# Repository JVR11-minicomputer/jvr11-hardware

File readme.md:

# JVR11 Homebrew Minicomputer - Hardware

This repository contains all schematics, PCB designs and PLD design sources of the JVR11, a homebrew minicomputer built around the DEC DCJ11 microprocessor. The computer will be built in multiple phases, each described in detail below.

All schematics and PCBs are designed in KiCad. All designs targeting SPLDs like the GAL16V8 and 22V10 are designed in WinCUPL, except the old sources, which were designed in GALASM. These will be replaced later. The CPLDs I used are all part of the ATF1504AS series, which can be used as an alternative to the MAX7000 series. All RTL is written in SystemVerilog and compiled using an older version of Quartus, targeting the MAX7000 series. The outputs were then converted to JEDEC using Atmel's POF2JED tool.

## Goals
### Phase 1: ODT Console    (FINISHED)

This is the very first stage of the project. My goal is to build a minimal but functional system capable of running a simple program. All the computer needs is a UART used to interact with the built-in ODT console and a little bit of SRAM to peek/poke into. This UART interface is built around the (Harris) 6402. Programs can be entered manually into memory and executed using this console, so no ROM is required. The ODT console itself is implemented in the processor's microcode.

The computer also needs to be able to load some startup configuration from a special register during its power-up sequence. A GAL22V10 is used as an interface to this register, I call it the "GP-interface". "GP" refers to the general-purpose cycles, which is a special kind of bus transaction that plays a big role during the power-up sequence. In addition, this interface is also responsible for generating the bus-reset signal and driving some status LEDs indicating whether the processor is in its "ODT mode" and also the results of the three microdiagnostics tests. All of this will be moved to the front panel later.

Known problems:
- The reset pin of the UART seems to be very sensitive to noise. When it is driven by the bus-reset signal, it starts to misbehave. This is because everything is still built on breadboards, which is definitely not ideal for this kind of builds. As a temporary solution, I connected a schmitt trigger inverter (74HCT14) to the active-low bus-reset to form a more stable reset signal for the UART. This inverter is probably not required anymore once the circuit moves to PCB, especially since the bus-reset signals will get buffered anyways.

### Phase 2: Bus Controller Upgrade     (IN PROGRESS)
In the previous phase, the computer used a single GAL16V8 to generate the bus access strobes (read enable, write enable etc). While being sufficient for a minimal functional system, it lacks a lot of functionality that we'll depend on later. This phase is all about implementing this missing functionality. First of all, it lacks the possibility to extend the cycle by inserting wait states. This will be required when interacting with slower IO devices and also in case of a cache miss. Second, since I'm planning to add DMA in the future, we need to support bus arbitration in order to be able to request mastership over the bus. Finally, we did not care about abort conditions. The internal MMU is capable of generating internal error conditions in which the remainder of the current cycle must be ignored and the access strobes are to be inhibited. An abort can also be generated by external hardware, but under specific conditions. In our case the system may report an error when referring to non-existent memory/IO or when writing to a read-only location or reading from a write-only location.

### Phase 3: Memory Subsystem     (FINISHED)
~~Every computer needs random-access memory. The J11 is capable of addressing 4MiB of physical memory of which the top 8K is reserved for memory-mapped IO. The remainder will be filled by RAM and a bit of ROM. Filling almost 4MiB with SRAM is practically possible with modern chips, but that would violate one of my most important constraints: keeping it as historically correct as possible. Therefore I will be using asynchronous DRAM.~~ 

~~Dynamic memory has two serious disadvantages: it's slow and needs periodic refreshes, or the data you stored will be lost. When it comes to refreshing the memory at regular intervals, I want to keep it as transparent to the CPU as possible by implementing a dedicated controller that runs on its own clock domain. When it comes down to the DRAM speeds, a single layer of write-back direct-mapped cache will be added which will act as a faster buffer between the fast system and its slow memory. The cache will offer 32KiB of SRAM to buffer both instructions and data (still unified), organized as 8K 32-bit cache blocks.~~

My original goal was to use DRAM for the system's main memory, using a dedicated controller that makes the access timing and refreshing completely transparent to the rest of the system. Since DRAM is slow, I wanted to introduce a write-back cache. I ended up moving the cache into the memory subsystem rather than keeping it local to the processor, which might sound like a questionable design choice (I admit it is), but it solved all coherency related problems because all memory accesses go through the same cache, even those initiated by the DMA controller.

I spent a couple of months working out a datapath and a control path and ended up with something that seamed to work, but it had some problems. The DRAM controller became a bottleneck, its worst-case latency was so high it was just unacceptable. I must mention one of my constraints for this project: I do not want to use any programmable logic device more capable than a simple MAX7000 CPLD with 64 macrocells. The overall performance can be greatly improved by designing a better DRAM controller, but that would require a lot more than 64 macrocells.

Improving the current memory system is simply impossible given my constraints, so I had to make a difficult decision: I decided to roll back to SRAM, which is simple to interface, fast enough to not need caching, but more importantly, it doesn't require a sophisticated memory subsystem anymore.

### Phase 4: IO Bridge  (IN PROGRESS)
Depending on the exact version, the J11 can run at a maximum clock speed of either 15MHz or 18MHz. That is way too fast to interface with slower IO controller chips directly. The simplest solution would be to rely on the wait state mechanism implemented by the bus controller to relax the speeds, but for write cycles that will cause stalls that could be avoided. Instead, a bridge can be added which buffers the write transactions targeting the slower IO devices behind it. The CPU can "deposit" the write data into this bridge at its full operating speed and resume execution while the IO bridge "proxies" that transaction on the slower bus. Unfortunately, read transfers cannot be buffered.

### Phase 5: Interrupts & DMA  (NOT STARTED)
The J11 supports vectored interrupts on multiple priority levels. A dedicated interrupt controller will be required to provide the vector address to the processor during an interrupt acknowledge cycle. I want those vector addresses to be fully programmable.

For high-throughput IO devices DMA can be used to transfer data without the processor's involvement. I want to build a flexible DMA controller that is fully programmable, has multiple channels with internal prioritization, can handle both 8 or 16 bit word sizes, can handle memory-to-memory transfers and can handle chained/scatter-gather transfers. The latter is required since the J11's internal MMU can map non-consecutive pages. Its design is inspired by the Motorola 68450 DMAC.

### Phase 6: Adding More IO  (NOT STARTED)
The most fundamental objective of this project is to build a minicomputer. While there is no real definition of what makes a computer a minicomputer, my interpretation of a minicomputer is a "big" computer that has multi-user capabilities and a lot of IO. From a hardware point of view, this is the moment where the homebrew computer turns into a proper minicomputer. With the IO bridge in place and interrupts and DMA being supported, it is finally time to start adding more and more IO devices to the system. I will add as much as I can, including: storage, timers, displays, sound, and more.

### Phase 7: VGA Subsystem  (NOT STARTED)
I always wanted to build my own VGA subsystem, so this is my chance. I got inspired by two unrelated video controllers: [James Sharman's VGA](https://youtube.com/playlist?list=PLFhc0MFC8MiD2QzxJKi_bHqwpGBZZpYCt&feature=shared) and the IBM PGA. James Sharman built a VGA controller completely from scratch, featuring advanced functionality such as scrolling, beam racing, tilemaps and more. The PGA on the other hand is a less-known video controller made by IBM that had a 8088 on board serving as a coprocessor. It could emulate a CGA, but more interestingly, it could be used to offload high-level commands. These two video controllers are completely different: on one hand we have complex functionality implemented in hardware and on the other we have software emulation. That raises one important question: Can we combine the best of both worlds? Can we build a VGA controller that implements complex functionality in hardware but also features a dedicated coprocessor that can offload things from the J11?

I don't have any concrete plans yet and I don't know how far I will take this, if I can even get to this point. But, I am sure about one thing: the 8088 is a great processor but if I were going to use a coprocessor I'd choose a less common processor. If possible, I want to keep it minicomputer-related. Or even better, DEC-related so both processors share some common history. That left me with one specific processor: the DEC DCT11. The J11 and the T11 both implement the PDP-11 instruction set, but other than that they do not have anything in common.

## Current Status (May 2026)
<br />

In the past two months I have been working on the IO bridge (right) and a new version of the core (left). At this moment, the prototype of the IO bridge is ready to be tested. I want to make sure the new version of the core is completely functional before integrating the IO bridge, hence the reason why the bridge isn't wired up to the computer just yet. 

The most important changes in the newest version computer's core are:
  -  **More memory**: The two 16KiB SRAM chips have been replaced by two 128KiB SRAM chips and ROM has been added.
  -  Bus buffers: In the previous version I used a set of 74x245 bidirectional buffers to drive the databus. Those are replaced by 74x541 unidirectional buffers, mainly for speed and to avoid brief contention when the direction changes while the outputs were active.
  -  **Address decoder**: The temporary decoder has been replaced by what I call the primary decoder. It is still an address decoder, but the main difference is that it selects larger subsystems (minimum 8KiB chunks) rather than individual peripherals like the UART. The new decoder can also generate aborts in case of non-existent memory or access violations (eg. writing to ROM). Until the IO bridge is in place, some temporary logic is used to decode the IO bridge select further down into a chip select for the ODT UART.
  - **Bus Error subsystem**: This is a small subsystem that can help the software to recover from bus errors. It latches additional context like the error type (4 bits) into a register that is readable by the processor and also serves as a configuration register that can enable or disable certain types of bus error. This register will be called the BER (Bus Error Recovery Register), which maps to a currently unused system register. This subsystem will not be used when the CPU is not the bus master since devices like the DMA will use its own error handling semantics.
  - **Bus controller**: The bus controller got a big upgrade. Its intent did not change, but it got a bit more sophisticated. In the last version the controller consisted of a MAX7000 CPLD and a 22V10 because this CPLD did not have enough pins to fit everything on a single chip. Now it has been replaced by a PLCC-84 version this CPLD, which offers more than enough usable pins.

**Next Steps:**

The new core has been built on breadboard and is almost ready to be tested. I am still writing the RTL for the new bus controller. Once the core is finished, the IO bridge can finally be integrated. After that, the next step would be the interrupt controller and finally moving existing parts of the build to PCB.

## Special thanks to PCBWay!
<br />

I would like to sincerely thank PCBWay for sponsoring this project. Their support has been invaluable in bringing this work to life. PCBWay is a leading manufacturer specializing in high-quality printed circuit boards, offering services ranging from rapid PCB prototyping to full-scale production. In addition to PCBs they also provide services like PCB assembly, CNC, 3D printing and more. 

I have been very pleased with the quality of the PCBs and SMD stencils I received. The precision, finish, and reliability exceeded my expectations. Overall, my experience with PCBWay has been excellent. Therefore I highly recommend others to check out [PCBWay](https://www.pcbway.com/) for their own projects.

<br />A picture of the boards I received: <br /><br />

## License
The content of this project is licensed under the [CERN-OHL-P version 2 license](https://cern-ohl.web.cern.ch/).

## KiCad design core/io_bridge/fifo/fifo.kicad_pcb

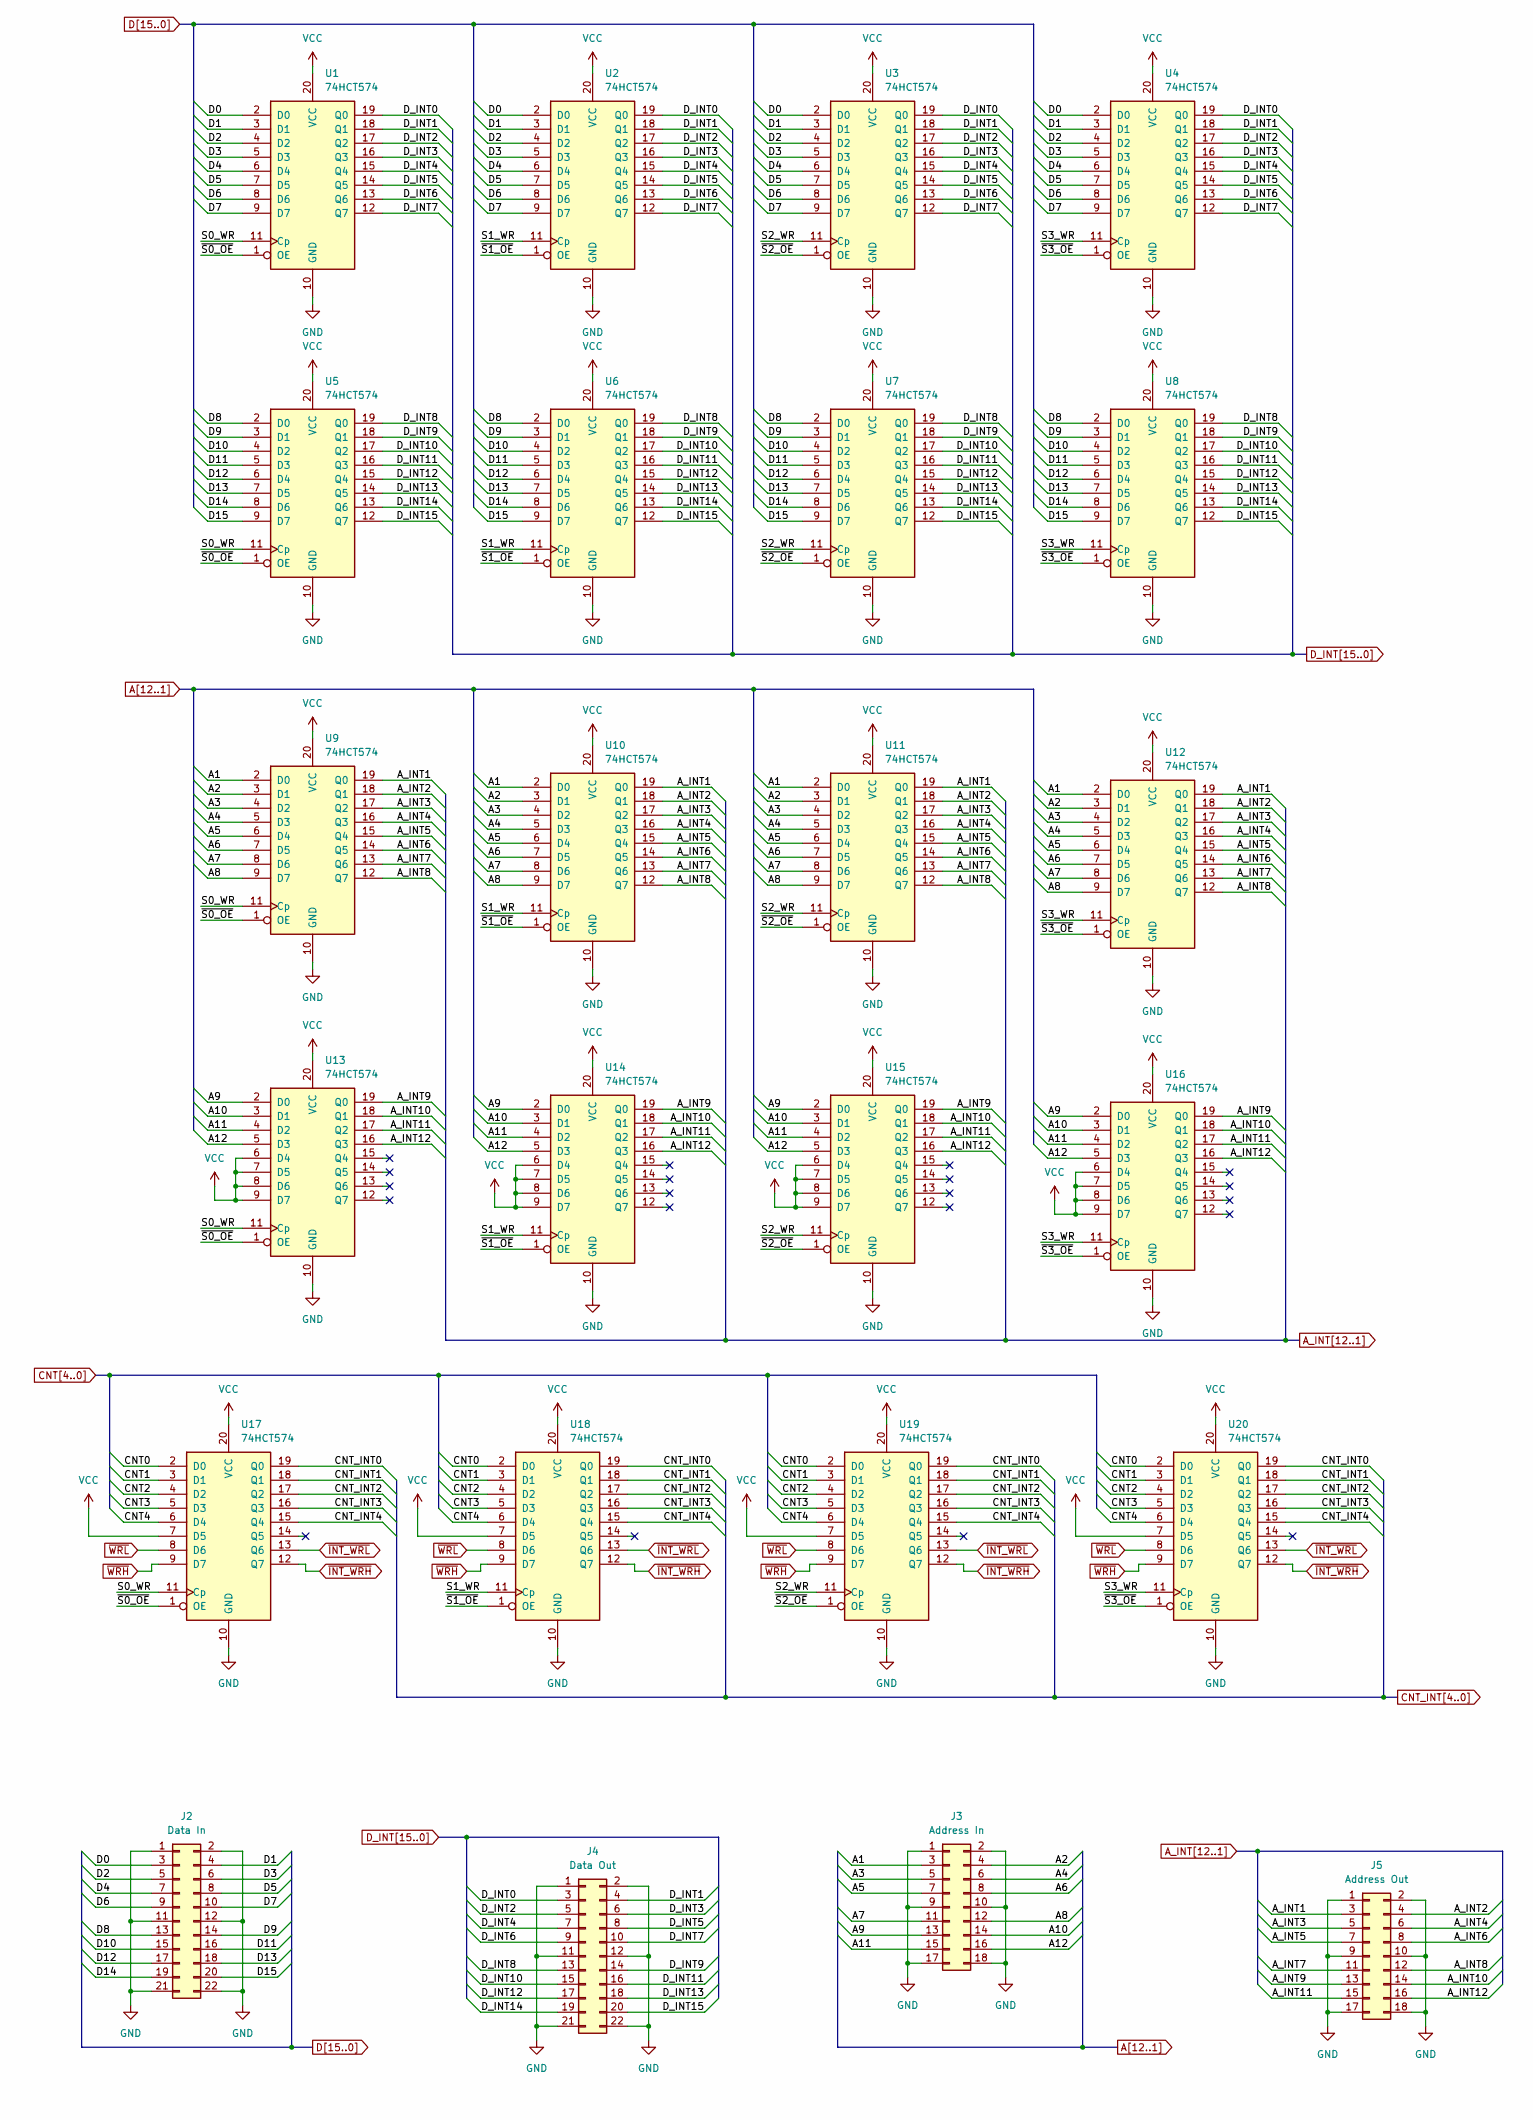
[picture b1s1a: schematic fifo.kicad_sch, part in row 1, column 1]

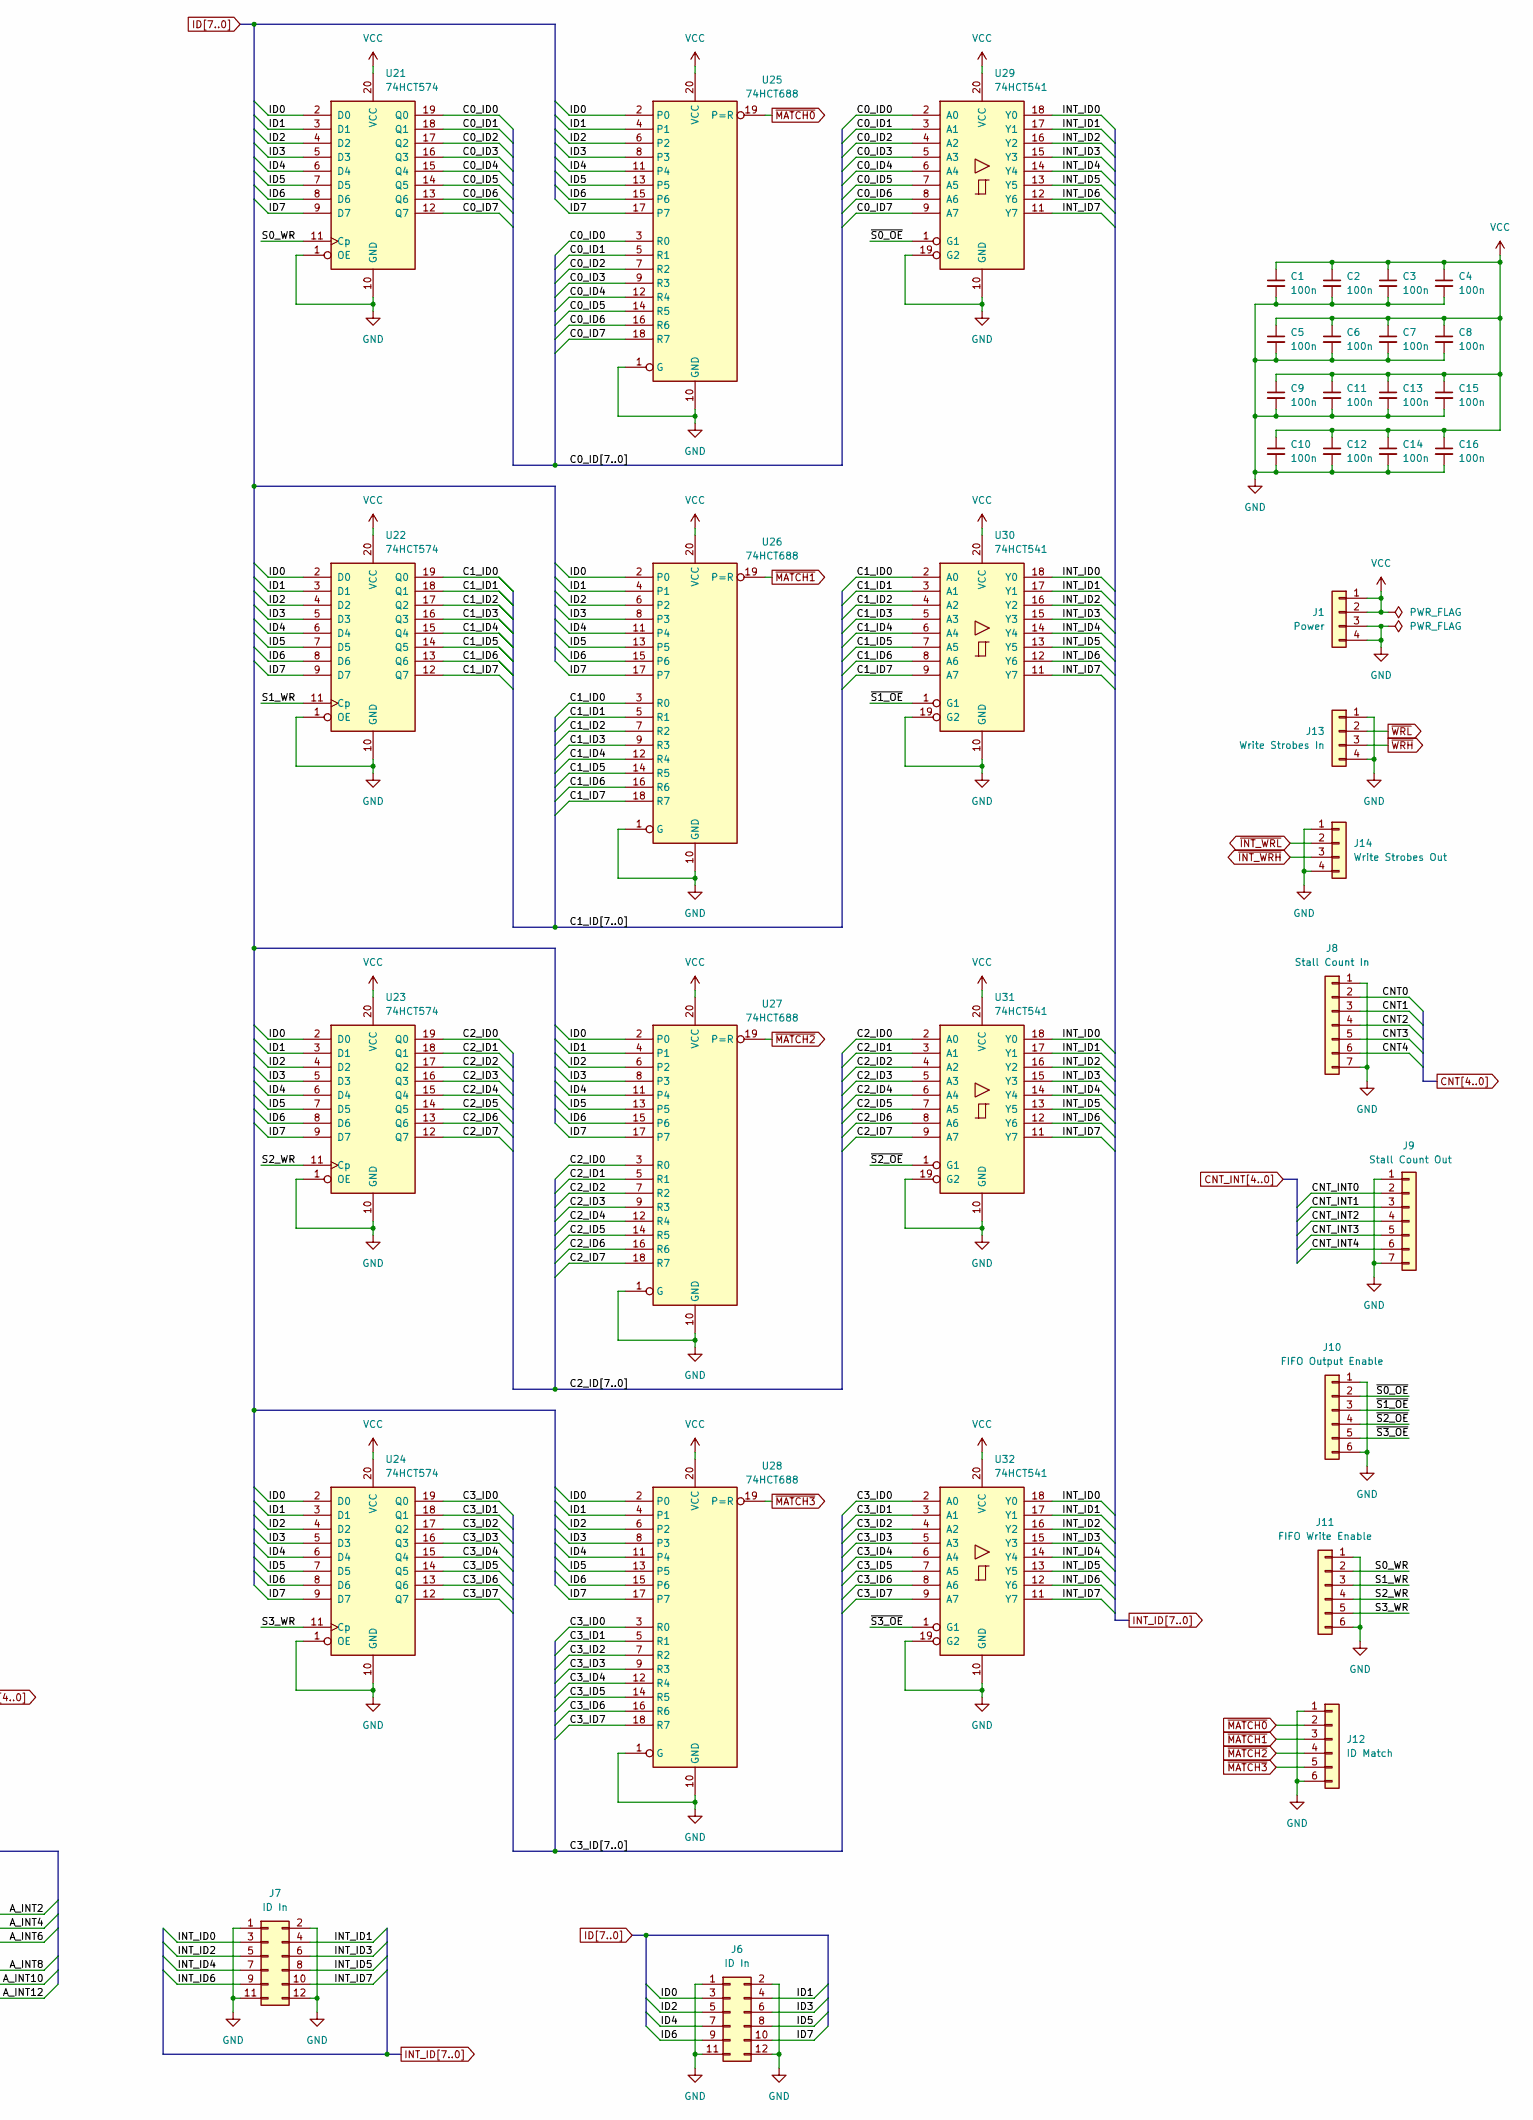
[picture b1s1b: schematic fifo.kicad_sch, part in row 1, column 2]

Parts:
C1, C2, C3, C4, C5, C6, C7, C8, C9, C10, C11, C12, C13, C14, C15, C16: 100n; C_0805_2012Metric_Pad1.18x1.45mm_HandSolder
J1: Power; PinHeader_1x04_P2.54mm_Vertical
J2: Data In; PinHeader_2x11_P2.54mm_Vertical
J3: Address In; PinHeader_2x09_P2.54mm_Vertical
J4: Data Out; PinHeader_2x11_P2.54mm_Vertical
J5: Address Out; PinHeader_2x09_P2.54mm_Vertical
J6, J7: ID In; PinHeader_2x06_P2.54mm_Vertical
J8: Stall Count In; PinHeader_1x07_P2.54mm_Vertical
J9: Stall Count Out; PinHeader_1x07_P2.54mm_Vertical
J10: FIFO Output Enable; PinHeader_1x06_P2.54mm_Vertical
J11: FIFO Write Enable; PinHeader_1x06_P2.54mm_Vertical
J12: ID Match; PinHeader_1x06_P2.54mm_Vertical
J13: Write Strobes In; PinHeader_1x04_P2.54mm_Vertical
J14: Write Strobes Out; PinHeader_1x04_P2.54mm_Vertical
U1, U2, U3, U4, U5, U6, U7, U8, U9, U10, U11, U12, U13, U14, U15, U16, U17, U18, U19, U20, U21, U22, U23, U24: 74HCT574; SOIC-20W_7.5x12.8mm_P1.27mm
U25, U26, U27, U28: 74HCT688; SOIC-20W_7.5x12.8mm_P1.27mm
U29, U30, U31, U32: 74HCT541; SOIC-20W_7.5x12.8mm_P1.27mm

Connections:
/C0_ID0: U21.19 (Q0), U25.3 (R0), U29.2 (A0)
/C0_ID1: U21.18 (Q1), U25.5 (R1), U29.3 (A1)
/C0_ID2: U21.17 (Q2), U25.7 (R2), U29.4 (A2)
/C0_ID3: U21.16 (Q3), U25.9 (R3), U29.5 (A3)
/C0_ID4: U21.15 (Q4), U25.12 (R4), U29.6 (A4)
/C0_ID5: U21.14 (Q5), U25.14 (R5), U29.7 (A5)
/C0_ID6: U21.13 (Q6), U25.16 (R6), U29.8 (A6)
/C0_ID7: U21.12 (Q7), U25.18 (R7), U29.9 (A7)
/C1_ID0: U22.19 (Q0), U26.3 (R0), U30.2 (A0)
/C1_ID1: U22.18 (Q1), U26.5 (R1), U30.3 (A1)
/C1_ID2: U22.17 (Q2), U26.7 (R2), U30.4 (A2)
/C1_ID3: U22.16 (Q3), U26.9 (R3), U30.5 (A3)
/C1_ID4: U22.15 (Q4), U26.12 (R4), U30.6 (A4)
/C1_ID5: U22.14 (Q5), U26.14 (R5), U30.7 (A5)
/C1_ID6: U22.13 (Q6), U26.16 (R6), U30.8 (A6)
/C1_ID7: U22.12 (Q7), U26.18 (R7), U30.9 (A7)
/C2_ID0: U23.19 (Q0), U27.3 (R0), U31.2 (A0)
/C2_ID1: U23.18 (Q1), U27.5 (R1), U31.3 (A1)
/C2_ID2: U23.17 (Q2), U27.7 (R2), U31.4 (A2)
/C2_ID3: U23.16 (Q3), U27.9 (R3), U31.5 (A3)
/C2_ID4: U23.15 (Q4), U27.12 (R4), U31.6 (A4)
/C2_ID5: U23.14 (Q5), U27.14 (R5), U31.7 (A5)
/C2_ID6: U23.13 (Q6), U27.16 (R6), U31.8 (A6)
/C2_ID7: U23.12 (Q7), U27.18 (R7), U31.9 (A7)
/C3_ID0: U24.19 (Q0), U28.3 (R0), U32.2 (A0)
/C3_ID1: U24.18 (Q1), U28.5 (R1), U32.3 (A1)
/C3_ID2: U24.17 (Q2), U28.7 (R2), U32.4 (A2)
/C3_ID3: U24.16 (Q3), U28.9 (R3), U32.5 (A3)
/C3_ID4: U24.15 (Q4), U28.12 (R4), U32.6 (A4)
/C3_ID5: U24.14 (Q5), U28.14 (R5), U32.7 (A5)
/C3_ID6: U24.13 (Q6), U28.16 (R6), U32.8 (A6)
/C3_ID7: U24.12 (Q7), U28.18 (R7), U32.9 (A7)
/S0_WR: J11.2, U1.11 (Cp), U5.11 (Cp), U9.11 (Cp), U13.11 (Cp), U17.11 (Cp), U21.11 (Cp)
/S1_WR: J11.3, U2.11 (Cp), U6.11 (Cp), U10.11 (Cp), U14.11 (Cp), U18.11 (Cp), U22.11 (Cp)
/S2_WR: J11.4, U3.11 (Cp), U7.11 (Cp), U11.11 (Cp), U15.11 (Cp), U19.11 (Cp), U23.11 (Cp)
/S3_WR: J11.5, U4.11 (Cp), U8.11 (Cp), U12.11 (Cp), U16.11 (Cp), U20.11 (Cp), U24.11 (Cp)
/~S0_OE: J10.2, U1.1 (OE), U5.1 (OE), U9.1 (OE), U13.1 (OE), U17.1 (OE), U29.1 (G1)
/~S1_OE: J10.3, U2.1 (OE), U6.1 (OE), U10.1 (OE), U14.1 (OE), U18.1 (OE), U30.1 (G1)
/~S2_OE: J10.4, U3.1 (OE), U7.1 (OE), U11.1 (OE), U15.1 (OE), U19.1 (OE), U31.1 (G1)
/~S3_OE: J10.5, U4.1 (OE), U8.1 (OE), U12.1 (OE), U16.1 (OE), U20.1 (OE), U32.1 (G1)
A1: J3.3, U9.2 (D0), U10.2 (D0), U11.2 (D0), U12.2 (D0)
A2: J3.4, U9.3 (D1), U10.3 (D1), U11.3 (D1), U12.3 (D1)
A3: J3.5, U9.4 (D2), U10.4 (D2), U11.4 (D2), U12.4 (D2)
A4: J3.6, U9.5 (D3), U10.5 (D3), U11.5 (D3), U12.5 (D3)
A5: J3.7, U9.6 (D4), U10.6 (D4), U11.6 (D4), U12.6 (D4)
A6: J3.8, U9.7 (D5), U10.7 (D5), U11.7 (D5), U12.7 (D5)
A7: J3.11, U9.8 (D6), U10.8 (D6), U11.8 (D6), U12.8 (D6)
A8: J3.12, U9.9 (D7), U10.9 (D7), U11.9 (D7), U12.9 (D7)
A9: J3.13, U13.2 (D0), U14.2 (D0), U15.2 (D0), U16.2 (D0)
A10: J3.14, U13.3 (D1), U14.3 (D1), U15.3 (D1), U16.3 (D1)
A11: J3.15, U13.4 (D2), U14.4 (D2), U15.4 (D2), U16.4 (D2)
A12: J3.16, U13.5 (D3), U14.5 (D3), U15.5 (D3), U16.5 (D3)
A_INT1: J5.3, U9.19 (Q0), U10.19 (Q0), U11.19 (Q0), U12.19 (Q0)
A_INT2: J5.4, U9.18 (Q1), U10.18 (Q1), U11.18 (Q1), U12.18 (Q1)
A_INT3: J5.5, U9.17 (Q2), U10.17 (Q2), U11.17 (Q2), U12.17 (Q2)
A_INT4: J5.6, U9.16 (Q3), U10.16 (Q3), U11.16 (Q3), U12.16 (Q3)
A_INT5: J5.7, U9.15 (Q4), U10.15 (Q4), U11.15 (Q4), U12.15 (Q4)
A_INT6: J5.8, U9.14 (Q5), U10.14 (Q5), U11.14 (Q5), U12.14 (Q5)
A_INT7: J5.11, U9.13 (Q6), U10.13 (Q6), U11.13 (Q6), U12.13 (Q6)
A_INT8: J5.12, U9.12 (Q7), U10.12 (Q7), U11.12 (Q7), U12.12 (Q7)
A_INT9: J5.13, U13.19 (Q0), U14.19 (Q0), U15.19 (Q0), U16.19 (Q0)
A_INT10: J5.14, U13.18 (Q1), U14.18 (Q1), U15.18 (Q1), U16.18 (Q1)
A_INT11: J5.15, U13.17 (Q2), U14.17 (Q2), U15.17 (Q2), U16.17 (Q2)
A_INT12: J5.16, U13.16 (Q3), U14.16 (Q3), U15.16 (Q3), U16.16 (Q3)
CNT0: J8.2, U17.2 (D0), U18.2 (D0), U19.2 (D0), U20.2 (D0)
CNT1: J8.3, U17.3 (D1), U18.3 (D1), U19.3 (D1), U20.3 (D1)
CNT2: J8.4, U17.4 (D2), U18.4 (D2), U19.4 (D2), U20.4 (D2)
CNT3: J8.5, U17.5 (D3), U18.5 (D3), U19.5 (D3), U20.5 (D3)
CNT4: J8.6, U17.6 (D4), U18.6 (D4), U19.6 (D4), U20.6 (D4)
CNT_INT0: J9.2, U17.19 (Q0), U18.19 (Q0), U19.19 (Q0), U20.19 (Q0)
CNT_INT1: J9.3, U17.18 (Q1), U18.18 (Q1), U19.18 (Q1), U20.18 (Q1)
CNT_INT2: J9.4, U17.17 (Q2), U18.17 (Q2), U19.17 (Q2), U20.17 (Q2)
CNT_INT3: J9.5, U17.16 (Q3), U18.16 (Q3), U19.16 (Q3), U20.16 (Q3)
CNT_INT4: J9.6, U17.15 (Q4), U18.15 (Q4), U19.15 (Q4), U20.15 (Q4)
D0: J2.3, U1.2 (D0), U2.2 (D0), U3.2 (D0), U4.2 (D0)
D1: J2.4, U1.3 (D1), U2.3 (D1), U3.3 (D1), U4.3 (D1)
D2: J2.5, U1.4 (D2), U2.4 (D2), U3.4 (D2), U4.4 (D2)
D3: J2.6, U1.5 (D3), U2.5 (D3), U3.5 (D3), U4.5 (D3)
D4: J2.7, U1.6 (D4), U2.6 (D4), U3.6 (D4), U4.6 (D4)
D5: J2.8, U1.7 (D5), U2.7 (D5), U3.7 (D5), U4.7 (D5)
D6: J2.9, U1.8 (D6), U2.8 (D6), U3.8 (D6), U4.8 (D6)
D7: J2.10, U1.9 (D7), U2.9 (D7), U3.9 (D7), U4.9 (D7)
D8: J2.13, U5.2 (D0), U6.2 (D0), U7.2 (D0), U8.2 (D0)
D9: J2.14, U5.3 (D1), U6.3 (D1), U7.3 (D1), U8.3 (D1)
D10: J2.15, U5.4 (D2), U6.4 (D2), U7.4 (D2), U8.4 (D2)
D11: J2.16, U5.5 (D3), U6.5 (D3), U7.5 (D3), U8.5 (D3)
D12: J2.17, U5.6 (D4), U6.6 (D4), U7.6 (D4), U8.6 (D4)
D13: J2.18, U5.7 (D5), U6.7 (D5), U7.7 (D5), U8.7 (D5)
D14: J2.19, U5.8 (D6), U6.8 (D6), U7.8 (D6), U8.8 (D6)
D15: J2.20, U5.9 (D7), U6.9 (D7), U7.9 (D7), U8.9 (D7)
D_INT0: J4.3, U1.19 (Q0), U2.19 (Q0), U3.19 (Q0), U4.19 (Q0)
D_INT1: J4.4, U1.18 (Q1), U2.18 (Q1), U3.18 (Q1), U4.18 (Q1)
D_INT2: J4.5, U1.17 (Q2), U2.17 (Q2), U3.17 (Q2), U4.17 (Q2)
D_INT3: J4.6, U1.16 (Q3), U2.16 (Q3), U3.16 (Q3), U4.16 (Q3)
D_INT4: J4.7, U1.15 (Q4), U2.15 (Q4), U3.15 (Q4), U4.15 (Q4)
D_INT5: J4.8, U1.14 (Q5), U2.14 (Q5), U3.14 (Q5), U4.14 (Q5)
D_INT6: J4.9, U1.13 (Q6), U2.13 (Q6), U3.13 (Q6), U4.13 (Q6)
D_INT7: J4.10, U1.12 (Q7), U2.12 (Q7), U3.12 (Q7), U4.12 (Q7)
D_INT8: J4.13, U5.19 (Q0), U6.19 (Q0), U7.19 (Q0), U8.19 (Q0)
D_INT9: J4.14, U5.18 (Q1), U6.18 (Q1), U7.18 (Q1), U8.18 (Q1)
D_INT10: J4.15, U5.17 (Q2), U6.17 (Q2), U7.17 (Q2), U8.17 (Q2)
D_INT11: J4.16, U5.16 (Q3), U6.16 (Q3), U7.16 (Q3), U8.16 (Q3)
D_INT12: J4.17, U5.15 (Q4), U6.15 (Q4), U7.15 (Q4), U8.15 (Q4)
D_INT13: J4.18, U5.14 (Q5), U6.14 (Q5), U7.14 (Q5), U8.14 (Q5)
D_INT14: J4.19, U5.13 (Q6), U6.13 (Q6), U7.13 (Q6), U8.13 (Q6)
D_INT15: J4.20, U5.12 (Q7), U6.12 (Q7), U7.12 (Q7), U8.12 (Q7)
GND: C1.2, C2.2, C3.2, C4.2, C5.2, C6.2, C7.2, C8.2, C9.2, C10.2, C11.2, C12.2, C13.2, C14.2, C15.2, C16.2, J1.3, J1.4, J2.1, J2.2, J2.11, J2.12, J2.21, J2.22, J3.1, J3.2, J3.9, J3.10, J3.17, J3.18, J4.1, J4.2, J4.11, J4.12, J4.21, J4.22, J5.1, J5.2, J5.9, J5.10, J5.17, J5.18, J6.1, J6.2, J6.11, J6.12, J7.1, J7.2, J7.11, J7.12, J8.1, J8.7, J9.1, J9.7, J10.1, J10.6, J11.1, J11.6, J12.1, J12.6, J13.1, J13.4, J14.1, J14.4, U1.10 (GND), U2.10 (GND), U3.10 (GND), U4.10 (GND), U5.10 (GND), U6.10 (GND), U7.10 (GND), U8.10 (GND), U9.10 (GND), U10.10 (GND), U11.10 (GND), U12.10 (GND), U13.10 (GND), U14.10 (GND), U15.10 (GND), U16.10 (GND), U17.10 (GND), U18.10 (GND), U19.10 (GND), U20.10 (GND), U21.1 (OE), U21.10 (GND), U22.1 (OE), U22.10 (GND), U23.1 (OE), U23.10 (GND), U24.1 (OE), U24.10 (GND), U25.1 (G), U25.10 (GND), U26.1 (G), U26.10 (GND), U27.1 (G), U27.10 (GND), U28.1 (G), U28.10 (GND), U29.10 (GND), U29.19 (G2), U30.10 (GND), U30.19 (G2), U31.10 (GND), U31.19 (G2), U32.10 (GND), U32.19 (G2)
ID0: J6.3, U21.2 (D0), U22.2 (D0), U23.2 (D0), U24.2 (D0), U25.2 (P0), U26.2 (P0), U27.2 (P0), U28.2 (P0)
ID1: J6.4, U21.3 (D1), U22.3 (D1), U23.3 (D1), U24.3 (D1), U25.4 (P1), U26.4 (P1), U27.4 (P1), U28.4 (P1)
ID2: J6.5, U21.4 (D2), U22.4 (D2), U23.4 (D2), U24.4 (D2), U25.6 (P2), U26.6 (P2), U27.6 (P2), U28.6 (P2)
ID3: J6.6, U21.5 (D3), U22.5 (D3), U23.5 (D3), U24.5 (D3), U25.8 (P3), U26.8 (P3), U27.8 (P3), U28.8 (P3)
ID4: J6.7, U21.6 (D4), U22.6 (D4), U23.6 (D4), U24.6 (D4), U25.11 (P4), U26.11 (P4), U27.11 (P4), U28.11 (P4)
ID5: J6.8, U21.7 (D5), U22.7 (D5), U23.7 (D5), U24.7 (D5), U25.13 (P5), U26.13 (P5), U27.13 (P5), U28.13 (P5)
ID6: J6.9, U21.8 (D6), U22.8 (D6), U23.8 (D6), U24.8 (D6), U25.15 (P6), U26.15 (P6), U27.15 (P6), U28.15 (P6)
ID7: J6.10, U21.9 (D7), U22.9 (D7), U23.9 (D7), U24.9 (D7), U25.17 (P7), U26.17 (P7), U27.17 (P7), U28.17 (P7)
INT_ID0: J7.3, U29.18 (Y0), U30.18 (Y0), U31.18 (Y0), U32.18 (Y0)
INT_ID1: J7.4, U29.17 (Y1), U30.17 (Y1), U31.17 (Y1), U32.17 (Y1)
INT_ID2: J7.5, U29.16 (Y2), U30.16 (Y2), U31.16 (Y2), U32.16 (Y2)
INT_ID3: J7.6, U29.15 (Y3), U30.15 (Y3), U31.15 (Y3), U32.15 (Y3)
INT_ID4: J7.7, U29.14 (Y4), U30.14 (Y4), U31.14 (Y4), U32.14 (Y4)
INT_ID5: J7.8, U29.13 (Y5), U30.13 (Y5), U31.13 (Y5), U32.13 (Y5)
INT_ID6: J7.9, U29.12 (Y6), U30.12 (Y6), U31.12 (Y6), U32.12 (Y6)
INT_ID7: J7.10, U29.11 (Y7), U30.11 (Y7), U31.11 (Y7), U32.11 (Y7)
VCC: C1.1, C2.1, C3.1, C4.1, C5.1, C6.1, C7.1, C8.1, C9.1, C10.1, C11.1, C12.1, C13.1, C14.1, C15.1, C16.1, J1.1, J1.2, U1.20 (VCC), U2.20 (VCC), U3.20 (VCC), U4.20 (VCC), U5.20 (VCC), U6.20 (VCC), U7.20 (VCC), U8.20 (VCC), U9.20 (VCC), U10.20 (VCC), U11.20 (VCC), U12.20 (VCC), U13.6 (D4), U13.7 (D5), U13.8 (D6), U13.9 (D7), U13.20 (VCC), U14.6 (D4), U14.7 (D5), U14.8 (D6), U14.9 (D7), U14.20 (VCC), U15.6 (D4), U15.7 (D5), U15.8 (D6), U15.9 (D7), U15.20 (VCC), U16.6 (D4), U16.7 (D5), U16.8 (D6), U16.9 (D7), U16.20 (VCC), U17.7 (D5), U17.20 (VCC), U18.7 (D5), U18.20 (VCC), U19.7 (D5), U19.20 (VCC), U20.7 (D5), U20.20 (VCC), U21.20 (VCC), U22.20 (VCC), U23.20 (VCC), U24.20 (VCC), U25.20 (VCC), U26.20 (VCC), U27.20 (VCC), U28.20 (VCC), U29.20 (VCC), U30.20 (VCC), U31.20 (VCC), U32.20 (VCC)
~INT_WRH: J14.3, U17.12 (Q7), U18.12 (Q7), U19.12 (Q7), U20.12 (Q7)
~INT_WRL: J14.2, U17.13 (Q6), U18.13 (Q6), U19.13 (Q6), U20.13 (Q6)
~MATCH0: J12.2, U25.19 (P=R)
~MATCH1: J12.3, U26.19 (P=R)
~MATCH2: J12.4, U27.19 (P=R)
~MATCH3: J12.5, U28.19 (P=R)
~WRH: J13.3, U17.9 (D7), U18.9 (D7), U19.9 (D7), U20.9 (D7)
~WRL: J13.2, U17.8 (D6), U18.8 (D6), U19.8 (D6), U20.8 (D6)

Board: 2 copper layers, 62 parts (0 on the bottom side), 132 nets, no tracks yet.
